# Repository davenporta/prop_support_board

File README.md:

# Prop Support Board
Michigan Aeronautial Science Association

Alex Davenport

### Capabilities
* 8x 12V Solenoid Valve Channels
* 8x Configurable Sensor Channels

### Sensor Channels
* Analog signal out to MCU's integrated ADC
* 3.3V, 5V, 12V, and 28V supply
* Asymmetrical 9-pin header connector
* Configurable with 6 types of sensor conditioning "daughter" boards

### Available Sensor Boards
* 3-wire Pressure Transducer w/ configurable excitation
* 4-wire Pressure Transducer w/ configurable excitation (WIP)
* T or K-type Thermocouples
* Load Cells
* RTDs (WIP)
* Capacitive Level Sensor (WIP)

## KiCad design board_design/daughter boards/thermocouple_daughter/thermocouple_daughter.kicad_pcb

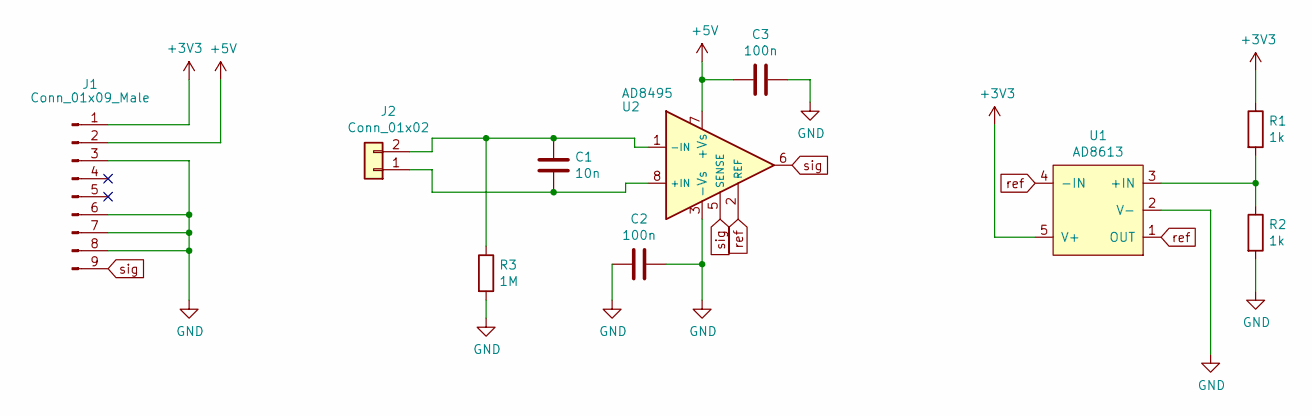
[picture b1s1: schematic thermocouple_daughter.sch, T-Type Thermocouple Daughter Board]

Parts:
C1: 10n; C_0805_2012Metric
C2, C3: 100n; C_0805_2012Metric
J1: Conn_01x09_Male; DaughterBoardConnector
J2: Conn_01x02; PCC-OST
R1, R2: 1k; R_0805_2012Metric
R3: 1M; R_0805_2012Metric
U1: AD8613; TSOT-23-5
U2: AD8495; MSOP-8_3x3mm_P0.65mm

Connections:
+3V3: J1.1, R1.1, U1.5 (V+)
+5V: C3.1, J1.2, U2.7 (+Vs)
GND: C2.1, C2.2, C3.2, J1.3, J1.6, J1.7, J1.8, R2.2, R3.2, U1.2 (V-), U2.3 (-Vs)
unnamed: C1.1, J2.2, R3.1, U2.1 (-IN)
unnamed: C1.2, J2.1, U2.8 (+IN)
unnamed: R1.2, R2.1, U1.3 (+IN)
unnamed: U1.1 (OUT), U1.4 (-IN), U2.2 (REF)
sig: J1.9, U2.5 (SENSE), U2.6

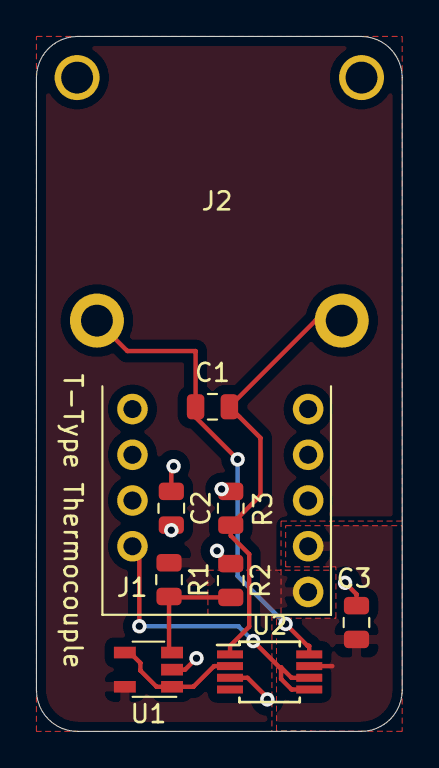
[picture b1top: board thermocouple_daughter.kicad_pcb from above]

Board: 2 copper layers, 20.3 x 38.6 mm, 10 parts (0 on the bottom side), 8 nets.

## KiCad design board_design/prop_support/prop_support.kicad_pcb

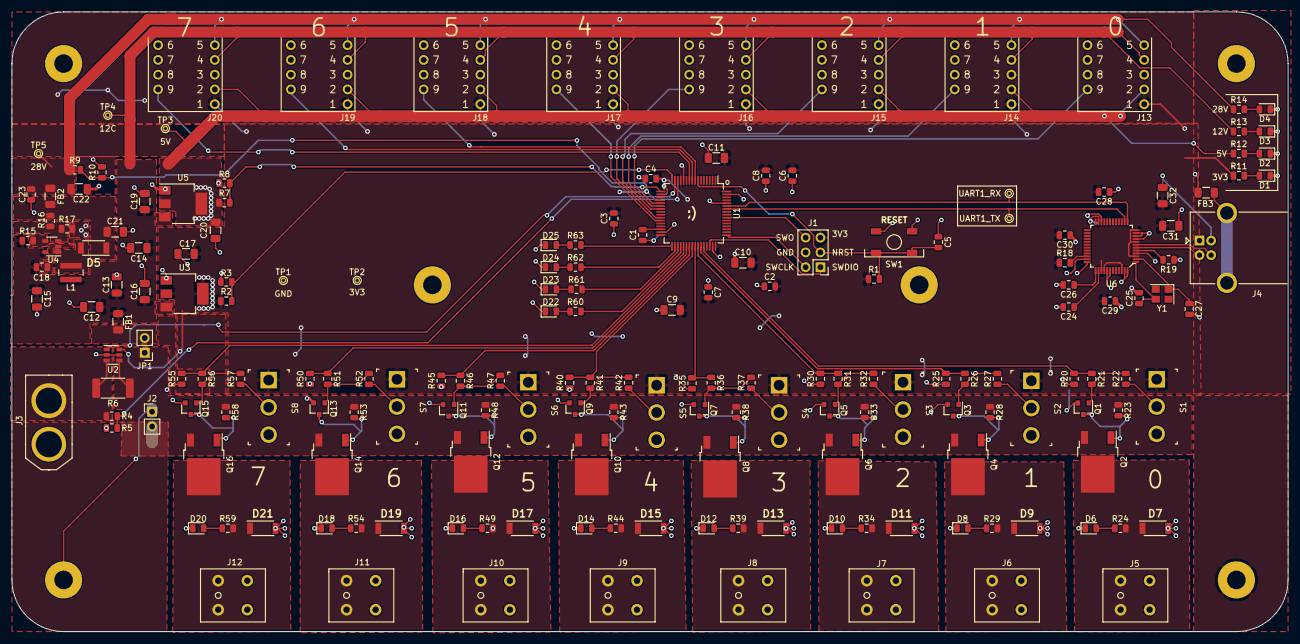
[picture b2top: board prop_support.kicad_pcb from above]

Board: 2 copper layers, 219.7 x 106.7 mm, 190 parts (0 on the bottom side), 102 nets.

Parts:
C1, C18: 4u7; C_0805_2012Metric
C2, C3, C4, C5, C6, C7, C8, C23, C24, C26, C28, C29, C30: 100n; C_0805_2012Metric
C9, C10, C11, C12, C13, C14, C15, C16, C17, C19, C20, C21, C22: 10u; C_1206_3216Metric
C25, C27: 18p; C_0805_2012Metric
C31, C32: 1u; C_1206_3216Metric
D1, D2, D3, D4, D6, D8, D10, D12, D14, D16, D18, D20, D22, D23, D24, D25: LED; LED_0805_2012Metric
D5: D_Schottky; SODFL4725X110N
D7, D9, D11, D13, D15, D17, D19, D21: D; SODFL4725X110N
FB1, FB2, FB3: Ferrite_Bead; R_1206_3216Metric
H1, H2, H3, H4, H5, H6: MountingHole_Pad; MountingHole_3.2mm_M3_Pad
J1: Conn_02x03_Counter_Clockwise; PinHeader_2x03_P2.54mm_Vertical
J2: GS2; PinHeader_1x02_P2.54mm_Vertical
J3: XT-60_female; XT60
J4: USB_B; USB_B_OST_USB-B1HSxx_Horizontal
J5, J6, J7, J8, J9, J10, J11, J12: Screw_Terminal_01x02; 1864435
J13, J14, J15, J16, J17, J18, J19, J20: Conn_01x09_Female; DaughterBoardConnector
JP1: Jumper; PinHeader_1x02_P2.54mm_Vertical
L1: 10uH; L_Wuerth_MAPI-4030
Q1, Q3, Q5, Q7, Q9, Q11, Q13, Q15: MMBT3904; SOT-23
Q2, Q4, Q6, Q8, Q10, Q12, Q14, Q16: Q_PMOS_GDS; TO-252-2
R1, R2, R3, R7, R8, R10, R11, R12, R18, R20, R21, R22, R23, R24, R25, R26, R27, R28, R29, R30, R31, R32, R33, R34, R35, R36, R37, R38, R39, R40, R41, R42, R43, R44, R45, R46, R47, R48, R49, R50, R51, R52, R53, R54, R55, R56, R57, R58, R59: 1k; R_0805_2012Metric
R4, R9, R13, R14: 10k; R_0805_2012Metric
R5: 3k3; R_0805_2012Metric
R6: 1m; R_2512_6332Metric
R15: 121k; R_0805_2012Metric
R16: 283k; R_0805_2012Metric
R17: 13k3; R_0805_2012Metric
R19: 12k1%; R_0805_2012Metric
R60, R61, R62, R63: 220; R_0805_2012Metric
S1, S2, S3, S4, S5, S6, S7, S8: 100SP3T1B1M2QE; Toggle_Switch_100SP1T1B4M2QE
SW1: SW_Push; SKQGADE010
TP1, TP2, TP3, TP4, TP5, TP6, TP7: TEST; TestPoint_THTPad_D1.0mm_Drill0.5mm
U1: STM32F446RETx; LQFP-64_10x10mm_P0.5mm
U2: INA181; SOT-23-6
U3: LM1117-3.3; SOT-223-3_TabPin2
U4: LT1930; SOT-23-5
U5: LM1117-5.0; SOT-223-3_TabPin2
U6: FT232H; LQFP-48_7x7mm
Y1: CX3225CA; Crystal_SMD_3225-4Pin_3.2x2.5mm

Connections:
+3V3: C2.2, C3.2, C4.2, C6.2, C7.2, C8.2, C9.2, C10.2, C11.2, C17.1, C28.2, C29.2, C30.2, C31.2, C32.2, J1.5, J13.1, J14.1, J15.1, J16.1, J17.1, J18.1, J19.1, J20.1, R1.1, R2.1, R11.1, R18.1, S1.1, S2.1, S3.1, S4.1, S5.1, S6.1, S7.1, S8.1, TP2.1, U1.13, U1.19, U1.32, U1.48, U1.64, U2.6, U3.2, U6.3, U6.8, U6.12, U6.24, U6.39, U6.40, U6.46
+5V: C20.1, J13.2, J14.2, J15.2, J16.2, J17.2, J18.2, J19.2, J20.2, R7.1, R12.1, TP3.1, U5.2
+12C: C12.1, C13.1, C14.1, C15.1, C16.1, C18.1, C19.1, FB1.1, J13.4, J14.4, J15.4, J16.4, J17.4, J18.4, J19.4, J20.4, L1.1, R13.1, R15.1, TP4.1, U3.3, U4.5, U5.3
+12V: JP1.1, Q2.3, Q4.3, Q6.3, Q8.3, Q10.3, Q12.3, Q14.3, Q16.3, R6.1, R23.1, R28.1, R33.1, R38.1, R43.1, R48.1, R53.1, R58.1, U2.4
+28V: C22.1, C23.1, FB2.1, J13.5, J14.5, J15.5, J16.5, J17.5, J18.5, J19.5, J20.5, R9.1, R14.1, TP5.1
GND: C1.2, C2.1, C3.1, C4.1, C5.1, C6.1, C7.1, C8.1, C9.1, C10.1, C11.1, C12.2, C13.2, C14.2, C15.2, C16.2, C17.2, C18.2, C19.2, C20.2, C21.2, C22.2, C23.2, C24.2, C25.2, C26.2, C27.2, C28.1, C29.1, C30.1, C31.1, C32.1, D1.1, D2.1, D3.1, D4.1, D22.1, D23.1, D24.1, D25.1, FB3.1, H1.1, H2.1, H3.1, H4.1, H5.1, H6.1, J1.4, J2.1, J4.4, J13.3, J13.6, J13.7, J13.8, J14.3, J14.6, J14.7, J14.8, J15.3, J15.6, J15.7, J15.8, J16.3, J16.6, J16.7, J16.8, J17.3, J17.6, J17.7, J17.8, J18.3, J18.6, J18.7, J18.8, J19.3, J19.6, J19.7, J19.8, J20.3, J20.6, J20.7, J20.8, Q1.2, Q3.2, Q5.2, Q7.2, Q9.2, Q11.2, Q13.2, Q15.2, R3.2, R8.2, R10.2, R17.2, R19.1, R20.1, R25.1, R30.1, R35.1, R40.1, R45.1, R50.1, R55.1, SW1.2, TP1.1, U1.12, U1.18, U1.31, U1.47, U1.60, U1.63, U2.2, U2.5, U3.1, U4.2, U5.1, U6.4, U6.9, U6.10, U6.11, U6.22, U6.23, U6.35, U6.36, U6.41, U6.42, U6.47, U6.48
GNDPWR: D6.1, D7.2, D8.1, D9.2, D10.1, D11.2, D12.1, D13.2, D14.1, D15.2, D16.1, D17.2, D18.1, D19.2, D20.1, D21.2, J2.2, J3.1, J5.2, J6.2, J7.2, J8.2, J9.2, J10.2, J11.2, J12.2, R5.2
LED_0: R60.2, U1.36
LED_1: R61.2, U1.35
LED_2: R62.2, U1.34
LED_3: R63.2, U1.33
NRST: C5.2, J1.3, R1.2, SW1.1, U1.7
unnamed: C1.1, U1.30
unnamed: C21.1, D5.1, FB2.2, R16.1
unnamed: C24.1, U6.38
unnamed: C25.1, U6.1, Y1.3
unnamed: C26.1, U6.37
unnamed: C27.1, U6.2, Y1.1
unnamed: D1.2, R11.2
unnamed: D2.2, R12.2
unnamed: D3.2, R13.2
unnamed: D4.2, R14.2
unnamed: D5.2, L1.2, U4.1
unnamed: D6.2, R24.1
unnamed: D8.2, R29.1
unnamed: D10.2, R34.1
unnamed: D12.2, R39.1
unnamed: D14.2, R44.1
unnamed: D16.2, R49.1
unnamed: D18.2, R54.1
unnamed: D20.2, R59.1
unnamed: D22.2, R60.1
unnamed: D23.2, R61.1
unnamed: D24.2, R62.1
unnamed: D25.2, R63.1
unnamed: FB1.2, JP1.2
unnamed: FB3.2, J4.5
unnamed: Q1.1, R21.2, R22.2
unnamed: Q1.3, Q2.1, R23.2
unnamed: Q3.1, R26.2, R27.2
unnamed: Q3.3, Q4.1, R28.2
unnamed: Q5.1, R31.2, R32.2
unnamed: Q5.3, Q6.1, R33.2
unnamed: Q7.1, R36.2, R37.2
unnamed: Q7.3, Q8.1, R38.2
unnamed: Q9.1, R41.2, R42.2
unnamed: Q9.3, Q10.1, R43.2
unnamed: Q11.1, R46.2, R47.2
unnamed: Q11.3, Q12.1, R48.2
unnamed: Q13.1, R51.2, R52.2
unnamed: Q13.3, Q14.1, R53.2
unnamed: Q15.1, R56.2, R57.2
unnamed: Q15.3, Q16.1, R58.2
unnamed: R15.2, U4.4
unnamed: R16.2, R17.1, U4.3
unnamed: R18.2, U6.34
unnamed: R19.2, U6.5
unnamed: R22.1, S1.2
unnamed: R27.1, S2.2
unnamed: R32.1, S3.2
unnamed: R37.1, S4.2
unnamed: R42.1, S5.2
unnamed: R47.1, S6.2
unnamed: R52.1, S7.2
unnamed: R57.1, S8.2
SWCLK: J1.2, U1.49
SWDIO: J1.1, U1.46
SWO: J1.6, U1.55
USART1_RX: TP6.1, U1.59, U6.13
USART1_TX: TP7.1, U1.58, U6.14
e3v3: R2.2, R3.1, U1.16
e5v: R7.2, R8.1, U1.17
e28v: R9.2, R10.1, U1.20
ebatt: R4.2, R5.1, U1.14
en_vlv0: R20.2, R21.1, U1.44
en_vlv1: R25.2, R26.1, U1.43
en_vlv2: R30.2, R31.1, U1.42
en_vlv3: R35.2, R36.1, U1.41
en_vlv4: R40.2, R41.1, U1.40
en_vlv5: R45.2, R46.1, U1.39
en_vlv6: R50.2, R51.1, U1.38
en_vlv7: R55.2, R56.1, U1.37
ibus: U1.15, U2.1
sig0: J13.9, U1.21
sig1: J14.9, U1.22
sig2: J15.9, U1.23
sig3: J16.9, U1.26
sig4: J17.9, U1.27
sig5: J18.9, U1.8
sig6: J19.9, U1.9
sig7: J20.9, U1.10
usb_data_n: J4.2, U6.6
usb_data_p: J4.3, U6.7
vbatt: J3.2, R4.1, R6.2, U2.3
vlv0p: D7.1, J5.1, Q2.2, R24.2
vlv1p: D9.1, J6.1, Q4.2, R29.2
vlv2p: D11.1, J7.1, Q6.2, R34.2
vlv3p: D13.1, J8.1, Q8.2, R39.2
vlv4p: D15.1, J9.1, Q10.2, R44.2
vlv5p: D17.1, J10.1, Q12.2, R49.2
vlv6p: D19.1, J11.1, Q14.2, R54.2
vlv7p: D21.1, J12.1, Q16.2, R59.2

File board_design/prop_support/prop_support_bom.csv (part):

"Source:","C:\Users\alexh\OneDrive\Desktop\masa\prop_support_board\prop_support\prop_support.sch"
"Date:","3/30/2019 3:33:55 PM"
"Tool:","Eeschema (5.1.0)-1"
"Generator:","C:\Program Files\KiCad\bin\scripting\plugins/bom_csv_grouped_by_value.py"
"Component Count:","183"

"Individual Components:"

"Item","Qty","Reference(s)","Value","LibPart","Footprint","Datasheet","Category","DK_Detail_Page","Description","Digi-Key_PN","Family","Manufacturer","Status"
"","","C1","4u7","Device:C","Capacitor_SMD:C_0805_2012Metric","~","","","","","","",""
"","","C2","100n","Device:C","Capacitor_SMD:C_0805_2012Metric","","","","","","","",""
"","","C3","100n","Device:C","Capacitor_SMD:C_0805_2012Metric","","","","","","","",""
"","","C4","100n","Device:C","Capacitor_SMD:C_0805_2012Metric","","","","","","","",""
"","","C5","100n","Device:C","Capacitor_SMD:C_0805_2012Metric","","","","","","","",""
"","","C6","100n","Device:C","Capacitor_SMD:C_0805_2012Metric","","","","","","","",""
"","","C7","100n","Device:C","Capacitor_SMD:C_0805_2012Metric","","","","","","","",""
"","","C8","100n","Device:C","Capacitor_SMD:C_0805_2012Metric","","","","","","","",""
"","","C9","10u","Device:C","Capacitor_SMD:C_1206_3216Metric","","","","","","","",""
"","","C10","10u","Device:C","Capacitor_SMD:C_1206_3216Metric","","","","","","","",""
"","","C11","10u","Device:C","Capacitor_SMD:C_1206_3216Metric","","","","","","","",""
"","","C12","10u","Device:C","Capacitor_SMD:C_1206_3216Metric","","","","","","","",""
"","","C13","10u","Device:C","Capacitor_SMD:C_1206_3216Metric","","","","","","","",""
"","","C14","10u","Device:C","Capacitor_SMD:C_1206_3216Metric","","","","","","","",""
"","","C15","10u","Device:C","Capacitor_SMD:C_1206_3216Metric","","","","","","","",""
"","","C16","10u","Device:C","Capacitor_SMD:C_1206_3216Metric","","","","","","","",""
"","","C17","10u","Device:C","Capacitor_SMD:C_1206_3216Metric","","","","","","","",""
"","","C18","4u7","Device:C","Capacitor_SMD:C_0805_2012Metric","~","","","","","","",""
"","","C19","10u","Device:C","Capacitor_SMD:C_1206_3216Metric","","","","","","","",""
"","","C20","10u","Device:C","Capacitor_SMD:C_1206_3216Metric","","","","","","","",""
"","","C21","10u","Device:C","Capacitor_SMD:C_1206_3216Metric","~","","","","","","",""
"","","C22","10u","Device:C","Capacitor_SMD:C_1206_3216Metric","~","","","","","","",""
"","","C23","100n","Device:C","Capacitor_SMD:C_0805_2012Metric","~","","","","","","",""
"","","C24","100n","Device:C","Capacitor_SMD:C_0805_2012Metric","~","","","","","","",""
"","","C25","18p","Device:C","Capacitor_SMD:C_0805_2012Metric","~","","","","","","",""
"","","C26","100n","Device:C","Capacitor_SMD:C_0805_2012Metric","~","","","","","","",""
"","","C27","18p","Device:C","Capacitor_SMD:C_0805_2012Metric","~","","","","","","",""
"","","C28","100n","Device:C","Capacitor_SMD:C_0805_2012Metric","","","","","","","",""
"","","C29","100n","Device:C","Capacitor_SMD:C_0805_2012Metric","","","","","","","",""
"","","C30","100n","Device:C","Capacitor_SMD:C_0805_2012Metric","","","","","","","",""
"","","C31","1u","Device:C","Capacitor_SMD:C_1206_3216Metric","","","","","","","",""
"","","C32","1u","Device:C","Capacitor_SMD:C_1206_3216Metric","","","","","","","",""
"","","D1","LED","Device:LED","LED_SMD:LED_0805_2012Metric","~","","","","","","",""
"","","D2","LED","Device:LED","LED_SMD:LED_0805_2012Metric","~","","","","","","",""
"","","D3","LED","Device:LED","LED_SMD:LED_0805_2012Metric","~","","","","","","",""
"","","D4","LED","Device:LED","LED_SMD:LED_0805_2012Metric","~","","","","","","",""
"","","D5","D_Schottky","Device:D_Schottky","davenport_kicad_footprints:SODFL4725X110N","~","","","","","","",""
"","","D6","LED","Device:LED","LED_SMD:LED_0805_2012Metric","~","","","","","","",""
"","","D7","D","Device:D","davenport_kicad_footprints:SODFL4725X110N","","","","","","","",""
"","","D8","LED","Device:LED","LED_SMD:LED_0805_2012Metric","~","","","","","","",""
"","","D9","D","Device:D","davenport_kicad_footprints:SODFL4725X110N","","","","","","","",""
"","","D10","LED","Device:LED","LED_SMD:LED_0805_2012Metric","~","","","","","","",""
"","","D11","D","Device:D","davenport_kicad_footprints:SODFL4725X110N","","","","","","","",""
"","","D12","LED","Device:LED","LED_SMD:LED_0805_2012Metric","~","","","","","","",""
"","","D13","D","Device:D","davenport_kicad_footprints:SODFL4725X110N","","","","","","","",""
"","","D14","LED","Device:LED","LED_SMD:LED_0805_2012Metric","~","","","","","","",""
"","","D15","D","Device:D","davenport_kicad_footprints:SODFL4725X110N","","","","","","","",""
"","","D16","LED","Device:LED","LED_SMD:LED_0805_2012Metric","~","","","","","","",""
"","","D17","D","Device:D","davenport_kicad_footprints:SODFL4725X110N","","","","","","","",""
"","","D18","LED","Device:LED","LED_SMD:LED_0805_2012Metric","~","","","","","","",""
"","","D19","D","Device:D","davenport_kicad_footprints:SODFL4725X110N","","","","","","","",""
"","","D20","LED","Device:LED","LED_SMD:LED_0805_2012Metric","~","","","","","","",""
"","","D21","D","Device:D","davenport_kicad_footprints:SODFL4725X110N","","","","","","","",""
"","","D22","LED","Device:LED","LED_SMD:LED_0805_2012Metric","","","","","","","",""
"","","D23","LED","Device:LED","LED_SMD:LED_0805_2012Metric","","","","","","","",""
"","","D24","LED","Device:LED","LED_SMD:LED_0805_2012Metric","","","","","","","",""
"","","D25","LED","Device:LED","LED_SMD:LED_0805_2012Metric","","","","","","","",""
"","","FB1","Ferrite_Bead","Device:Ferrite_Bead","Resistor_SMD:R_1206_3216Metric","~","","","","","","",""
"","","FB2","Ferrite_Bead","Device:Ferrite_Bead","Resistor_SMD:R_1206_3216Metric","~","","","","","","",""
"","","FB3","Ferrite_Bead","Device:Ferrite_Bead","Resistor_SMD:R_1206_3216Metric","~","","","","","","",""
"","","H1","MountingHole_Pad","Mechanical:MountingHole_Pad","MountingHole:MountingHole_3.2mm_M3_Pad","~","","","","","","",""
"","","H2","MountingHole_Pad","Mechanical:MountingHole_Pad","MountingHole:MountingHole_3.2mm_M3_Pad","~","","","","","","",""
"","","H3","MountingHole_Pad","Mechanical:MountingHole_Pad","MountingHole:MountingHole_3.2mm_M3_Pad","~","","","","","","",""
"","","H4","MountingHole_Pad","Mechanical:MountingHole_Pad","MountingHole:MountingHole_3.2mm_M3_Pad","~","","","","","","",""
"","","H5","MountingHole_Pad","Mechanical:MountingHole_Pad","MountingHole:MountingHole_3.2mm_M3_Pad","~","","","","","","",""
"","","H6","MountingHole_Pad","Mechanical:MountingHole_Pad","MountingHole:MountingHole_3.2mm_M3_Pad","~","","","","","","",""
"","","J1","Conn_02x03_Counter_Clockwise","Connector_Generic:Conn_02x03_Counter_Clockwise","Connector_PinHeader_1.00mm:PinHeader_2x03_P1.00mm_Vertical","","","","","","","",""
"","","J2","GS2","Device:Jumper","Connector_PinHeader_1.00mm:PinHeader_1x02_P1.00mm_Vertical","","","","","","","",""
"","","J3","XT-60_female","davenport-kicad:XT-60_female","davenport_kicad_footprints:XT60","","","","","","","",""
"","","J4","USB_B","Connector:USB_B","Connector_USB:USB_B_OST_USB-B1HSxx_Horizontal"," ~","","","","","","",""
"","","J5","Screw_Terminal_01x02","Connector:Screw_Terminal_01x02","Connector_Phoenix_MSTB:PhoenixContact_MSTBVA_2,5_2-G_1x02_P5.00mm_Vertical","~","","","","","","",""
"","","J6","Screw_Terminal_01x02","Connector:Screw_Terminal_01x02","Connector_Phoenix_MSTB:PhoenixContact_MSTBVA_2,5_2-G_1x02_P5.00mm_Vertical","~","","","","","","",""
"","","J7","Screw_Terminal_01x02","Connector:Screw_Terminal_01x02","Connector_Phoenix_MSTB:PhoenixContact_MSTBVA_2,5_2-G_1x02_P5.00mm_Vertical","~","","","","","","",""
"","","J8","Screw_Terminal_01x02","Connector:Screw_Terminal_01x02","Connector_Phoenix_MSTB:PhoenixContact_MSTBVA_2,5_2-G_1x02_P5.00mm_Vertical","~","","","","","","",""
"","","J9","Screw_Terminal_01x02","Connector:Screw_Terminal_01x02","Connector_Phoenix_MSTB:PhoenixContact_MSTBVA_2,5_2-G_1x02_P5.00mm_Vertical","~","","","","","","",""
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
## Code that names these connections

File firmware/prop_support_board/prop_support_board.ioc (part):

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Mcu.Name=STM32F446R(C-E)Tx
Mcu.Package=LQFP64
Mcu.UserName=STM32F446RETx
PA0-WKUP.Signal=ADCx_IN0
PA1.Signal=ADCx_IN1
PA10.GPIOParameters=GPIO_Label
PA10.GPIO_Label=en_vlv1
PA10.Signal=GPIO_Output
PA11.GPIOParameters=GPIO_Label
PA11.GPIO_Label=en_vlv0
PA11.Signal=GPIO_Output
PA13.Mode=Trace_Asynchronous_SW
PA13.Signal=SYS_JTMS-SWDIO
PA14.Mode=Trace_Asynchronous_SW
PA14.Signal=SYS_JTCK-SWCLK
PA2.Signal=ADCx_IN2
PA3.Signal=ADCx_IN3
PA4.Signal=ADCx_IN4
PA5.Signal=ADCx_IN5
PA6.Signal=ADCx_IN6
PA7.Signal=ADCx_IN7
PA8.GPIOParameters=GPIO_Label
PA8.GPIO_Label=en_vlv3
PA8.Signal=GPIO_Output
PA9.GPIOParameters=GPIO_Label
PA9.GPIO_Label=en_vlv2
PA9.Signal=GPIO_Output
PB0.Signal=ADCx_IN8
PB1.Signal=ADCx_IN9
PB12.GPIOParameters=GPIO_Label
PB12.GPIO_Label=led3
PB12.Signal=GPIO_Output
PB13.GPIOParameters=GPIO_Label
PB13.GPIO_Label=led2
PB13.Signal=GPIO_Output
PB14.GPIOParameters=GPIO_Label
PB14.GPIO_Label=led1
PB14.Signal=GPIO_Output
PB15.GPIOParameters=GPIO_Label
PB15.GPIO_Label=led0
PB15.Signal=GPIO_Output
PB3.Mode=Trace_Asynchronous_SW
PB3.Signal=SYS_JTDO-SWO
PB6.Mode=Asynchronous
PB6.Signal=USART1_TX
PB7.Mode=Asynchronous
PB7.Signal=USART1_RX
PC0.Signal=ADCx_IN10
PC1.Signal=ADCx_IN11
PC2.Signal=ADCx_IN12
PC6.GPIOParameters=GPIO_Label
PC6.GPIO_Label=en_vlv7
PC6.Signal=GPIO_Output
PC7.GPIOParameters=GPIO_Label
PC7.GPIO_Label=en_vlv6
PC7.Signal=GPIO_Output
PC8.GPIOParameters=GPIO_Label
PC8.GPIO_Label=en_vlv5
PC8.Signal=GPIO_Output
PC9.GPIOParameters=GPIO_Label
PC9.GPIO_Label=en_vlv4
PC9.Signal=GPIO_Output
RCC.SYSCLKFreq_VALUE=24000000
RCC.SYSCLKSource=RCC_SYSCLKSOURCE_PLLCLK
board=custom

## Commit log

2019-04-02 reorganization
2019-04-03 added daughter board kicad projects
2019-04-04 3 boards down...
2019-04-09 first MX export
2019-04-09 changes to toolchain
2019-04-09 screenshot added
2019-04-09 Updated Master Sheet
2019-04-09 gui copied from nsternie/live_telemetry
    Copied over some of my previous work from the live telem project as a framework for this gui
2019-09-13 push for jack
2019-09-13 Update LICENSE
2019-11-20 port project to STM32CubeIDE
